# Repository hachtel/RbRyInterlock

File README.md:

# RbRyInterlock
This project is a PCB centered around the ESP8266 board.The board is intended to take an analog signal on the A0 pin (e.g. from a photodiode), discriminate if the signal is above some threshold and toggle a digital output. Since the Moglabs TA interlock references its own +5V and GND we are using this control signal to modulate a mechanical relay to short or open the interlock.
## A few key features:
- A level converter is required as the mechanical relay switches at a voltage larger than the microprocessor supplies, thus we boost the 3.3V signal to 5V. 
- There is a BNC header (updated using JQI BNC connector footprint for better mechanical stability) to bring in the signal from the photodiode. 
- To ensure that the board is a single layer we have inserted a ground plane. 
- The original design used linear voltage regulators to condition +15V down to +5V. These were running too hot, so we have added solder pads 1/2 for +5V/GND. We have found that a standard AC/DC wall adapter works well for this purpose.

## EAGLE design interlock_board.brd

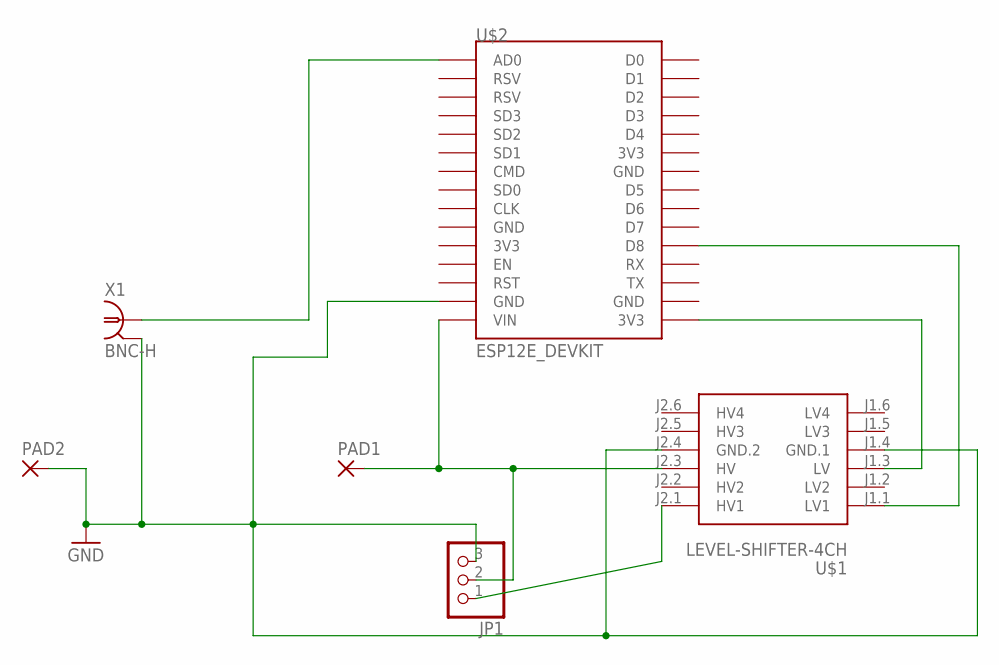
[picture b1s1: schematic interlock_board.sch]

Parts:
JP1: PINHD-1X3; 1X03
PAD1, PAD2: 2,54/0,9
U$1: LEVEL-SHIFTER-4CH
U$2: ESP12E_DEVKIT
X1: BNC-H; BNC90

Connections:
GND: JP1.3, PAD2.1, U$1.J1.4 (GND.1), U$1.J2.4 (GND.2), U$2.GND@1 (GND), X1.2
unnamed: JP1.2, PAD1.1, U$1.J2.3 (HV), U$2.VIN
unnamed: U$1.J1.3 (LV), U$2.3V3@2 (3V3)
unnamed: U$1.J1.1 (LV1), U$2.D8
unnamed: U$2.AD0, X1.1
unnamed: JP1.1, U$1.J2.1 (HV1)

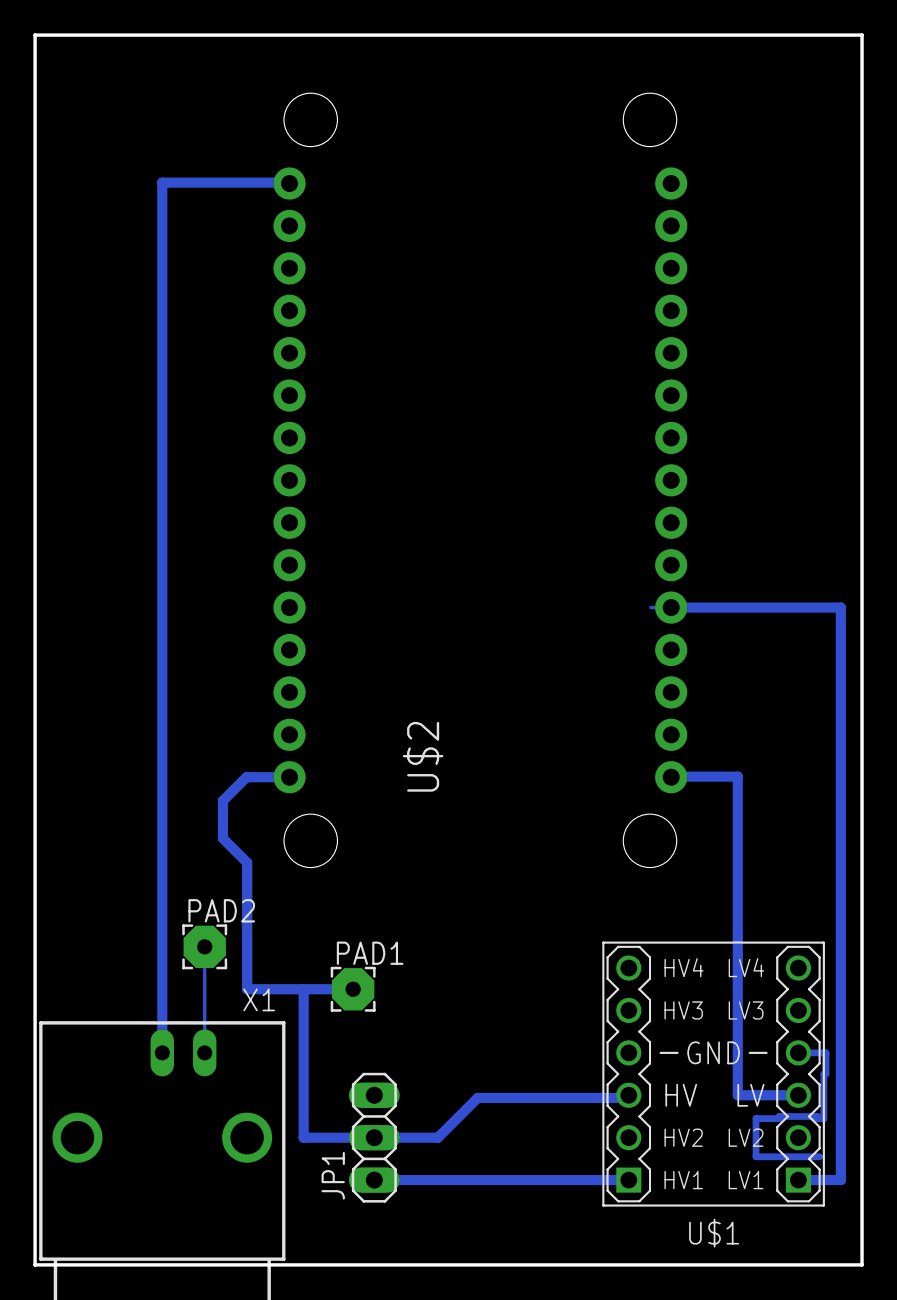
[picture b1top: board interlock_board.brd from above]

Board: 2 copper layers, 49.5 x 73.7 mm, 6 parts (0 on the bottom side), 6 nets.

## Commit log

2019-05-01 Added EAGLE files
2019-05-01 Added microprocessor code
2019-05-01 Update interlock_board.brd
    Moved various wires so they are not as close to the various pins on the board.
2019-05-08 Update with Alessandro's help
    This update increases the copper trace size from 0.008" to 0.024" and moves them to the bottom layer, uses an updated BNC connector footprint (from JQI library) for better mechanical stability, and i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
2019-05-08 Update README.md
    Added new information after printing with Alessandro.

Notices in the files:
parts and their libraries:
diy-modules: Released under the Creative Commons Attribution 4.0 International License: http://creativecommons.org/licenses/by/4.0
